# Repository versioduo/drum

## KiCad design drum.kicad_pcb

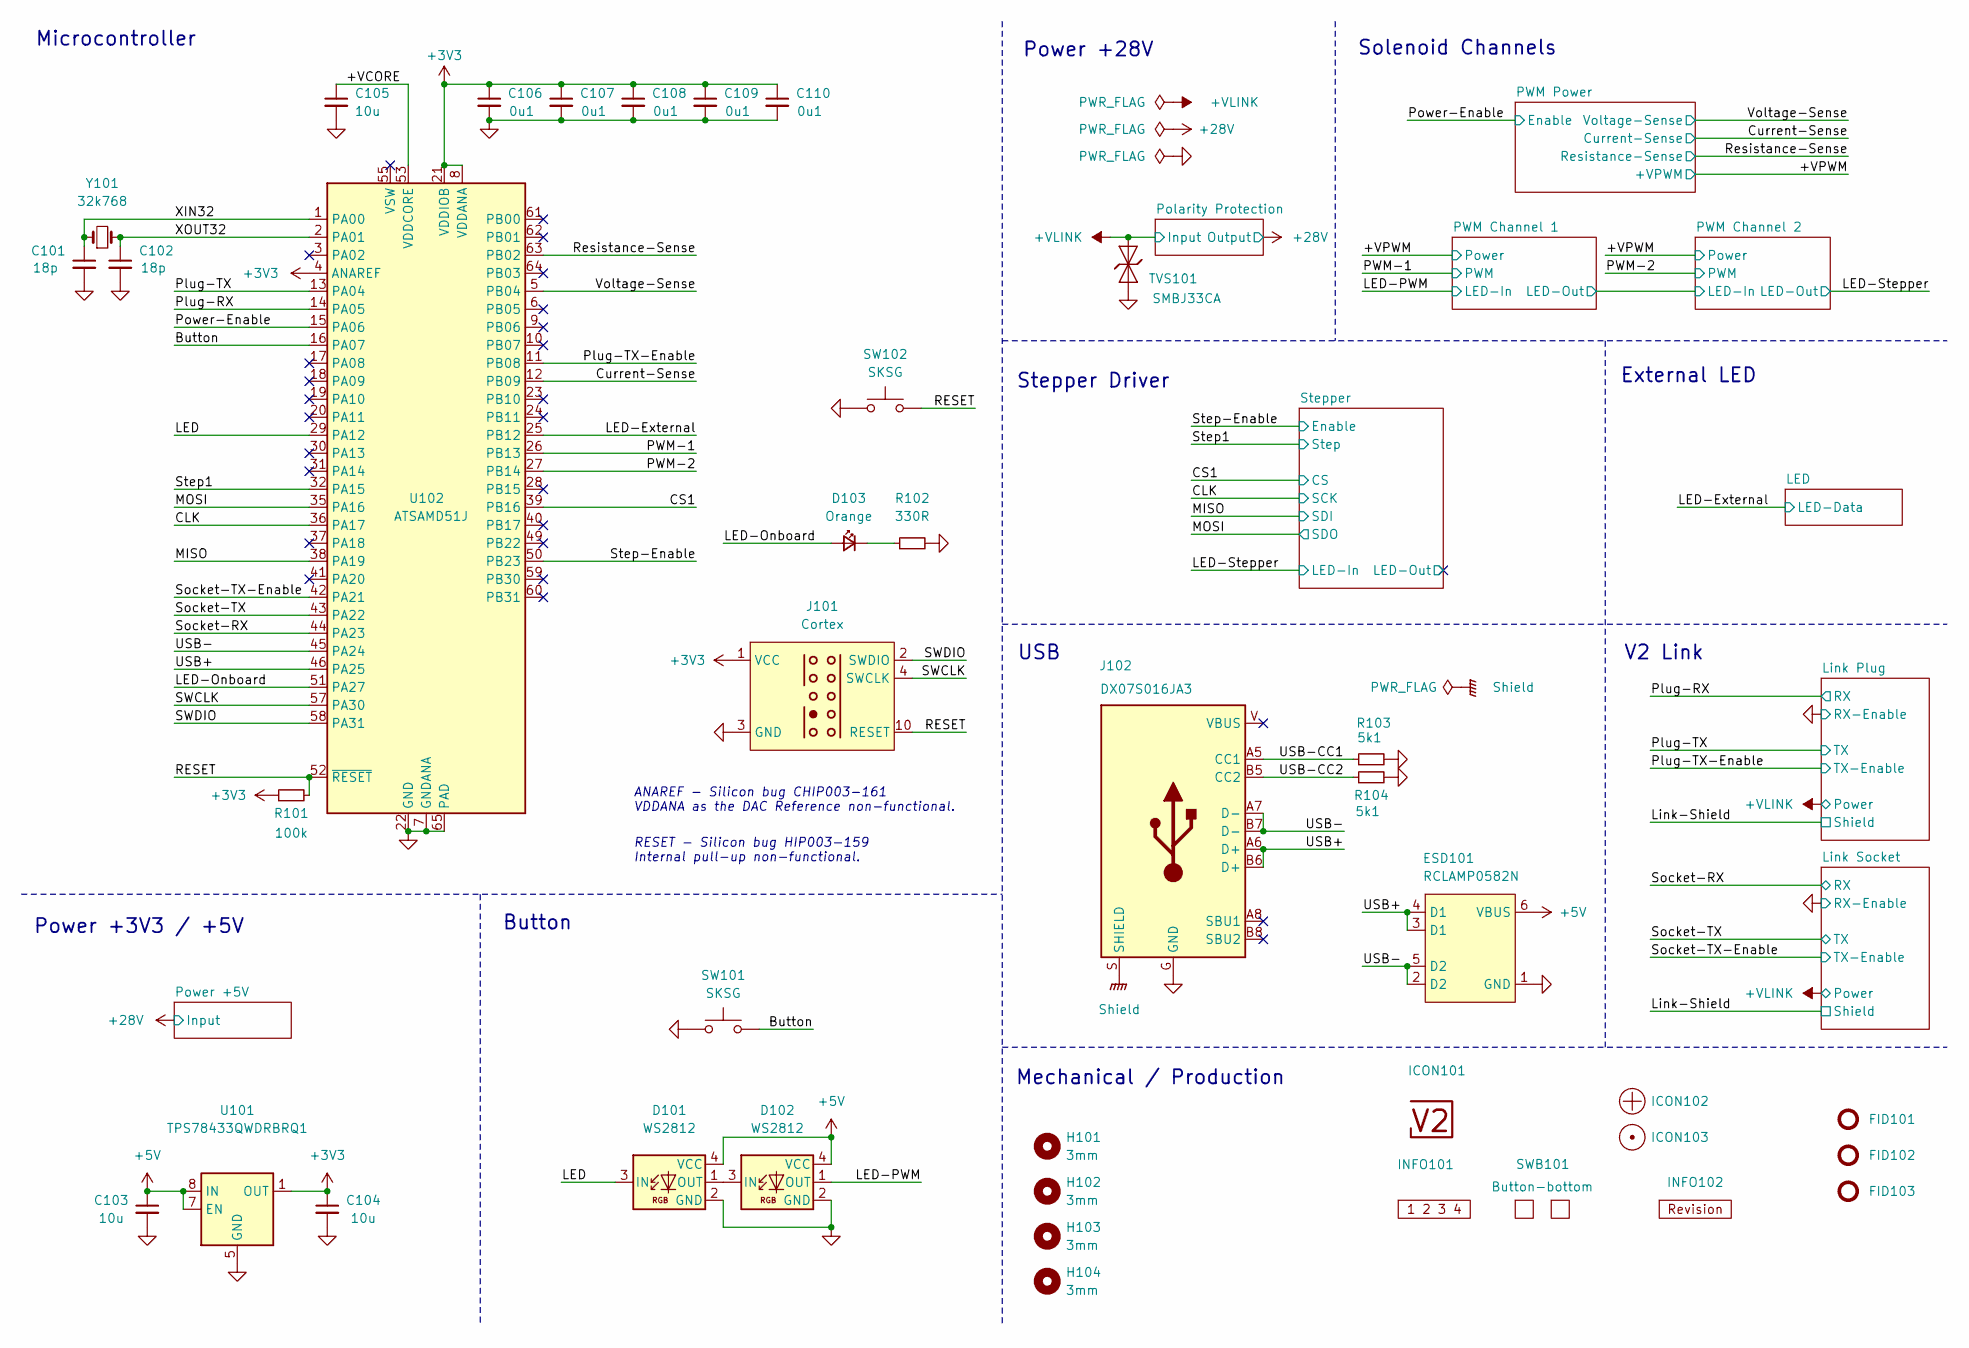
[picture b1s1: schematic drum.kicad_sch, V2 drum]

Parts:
C101, C102: 18p; C_1608; Rating 50V; Mouser 810-CGA3E2C0G1H180J
C103, C104: 10u; C_2012; Rating 25V; Mouser 810-C2012X5R1E106K
C105: 10u; C_1608; Rating 10V; Mouser 810-C1608X6S1A106M
C106, C107, C108, C109, C110: 0u1; C_1608; Rating 50V; Mouser 810-CGA3E2X7R1H104MA
D101, D102: WS2812; WS2812-2020; Rating 15mA; LCSC C965555
D103: Orange; LED_1608; Rating 605nm; Mouser 755-SML-D12D1WT86
ESD101: RCLAMP0582N; SLP1210N6; Rating 20kV; Mouser 947-RCLAMP0582N.TCT
FID101, FID102, FID103: Fiducial_Paste; Fiducial_0.5mm_Mask1mm_Paste
H101, H102, H103, H104: 3mm; MountingHole_3mm
ICON101: V2-logo; Logo_Small
ICON102: Plus; Plus_Small
ICON103: Dot; Dot_Small
INFO101: Layer_Numbers-6
INFO102: Revision
J101: Cortex
J102: DX07S016JA3; JAE_DX07S016JA3; Rating USB2.0; Mouser 656-DX07S016JA3R1500
R101: 100k; R_1608; Rating 100mW; Mouser 71-CRCW0603100KFKEAC
R102: 330R; R_1608; Rating 100mW; Mouser 71-CRCW0603330RFKEAC
R103, R104: 5k1; R_1608; Rating 100mW; Mouser 71-CRCW06035K10FKEAC
SW101, SW102: SKSG; Rating 1.6N; Mouser 688-SKSGACE010
SWB101: Button-bottom; PCB_Button-bottom
TVS101: SMBJ33CA; D_SMB; Rating 33V; Mouser 652-SMBJ33CA-Q
U101: TPS78433QWDRBRQ1; VSON-8-1_3x3mm_P0.65_EP1.65x2.4mm; Rating 300mA; Mouser 595-TPS78433QWDRBRQ1
U102: ATSAMD51J; QFN-64-1EP_9x9mm_P0.5mm_EP4.8x4.8mm_ThermalVias; Rating Cortex-M4F; Mouser 556-ATSAMD51J19AMU
Y101: 32k768; Crystal_SMD_3215-2Pin_3.2x1.5mm; Rating 10ppm; Mouser 815-ABS0716632.768KT

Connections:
+3V3: C104.1, C106.1, C107.1, C108.1, C109.1, C110.1, J101.1 (VCC), R101.1, U101.1 (OUT), U102.4 (ANAREF), U102.8 (VDDANA), U102.21 (VDDIOB), U102.34 (VDDIO), U102.48 (VDDIO), U102.56 (VDDIO); also elsewhere on the board
+5V: C103.1, D101.4 (VCC), D102.4 (VCC), ESD101.6 (VBUS), U101.6 (EN), U101.7 (EN), U101.8 (IN); also elsewhere on the board
/+VCORE: C105.1, U102.53 (VDDCORE)
/+VLINK: TVS101.2 (A); also elsewhere on the board
/Button: SW101.2, U102.16 (PA07)
/CLK: U102.36 (PA17); also elsewhere on the board
/CS1: U102.39 (PB16); also elsewhere on the board
/Current-Sense: U102.12 (PB09); also elsewhere on the board
/LED: D101.3 (IN), U102.29 (PA12)
/LED-External: U102.25 (PB12); also elsewhere on the board
/LED-Onboard: D103.2 (A), U102.51 (PA27)
/LED-PWM: D102.1 (OUT); also elsewhere on the board
/MISO: U102.38 (PA19); also elsewhere on the board
/MOSI: U102.35 (PA16); also elsewhere on the board
/PWM-1: U102.26 (PB13); also elsewhere on the board
/PWM-2: U102.27 (PB14); also elsewhere on the board
/Plug-RX: U102.14 (PA05); also elsewhere on the board
/Plug-TX: U102.13 (PA04); also elsewhere on the board
/Plug-TX-Enable: U102.11 (PB08); also elsewhere on the board
/Power-Enable: U102.15 (PA06); also elsewhere on the board
/RESET: J101.10 (RESET), R101.2, SW102.2, U102.52 (~RESET)
/Resistance-Sense: U102.63 (PB02); also elsewhere on the board
/SWCLK: J101.4 (SWCLK), U102.57 (PA30)
/SWDIO: J101.2 (SWDIO), U102.58 (PA31)
/Shield: J102.S (SHIELD)
/Socket-RX: U102.44 (PA23); also elsewhere on the board
/Socket-TX: U102.43 (PA22); also elsewhere on the board
/Socket-TX-Enable: U102.42 (PA21); also elsewhere on the board
/Step1: U102.32 (PA15); also elsewhere on the board
/Step-Enable: U102.50 (PB23); also elsewhere on the board
/USB+: ESD101.3 (D1), ESD101.4 (D1), J102.A6 (D+), J102.B6 (D+), U102.46 (PA25)
/USB-: ESD101.2 (D2), ESD101.5 (D2), J102.A7 (D-), J102.B7 (D-), U102.45 (PA24)
/USB-CC1: J102.A5 (CC1), R103.1
/USB-CC2: J102.B5 (CC2), R104.1
/Voltage-Sense: U102.5 (PB04); also elsewhere on the board
/XIN32: C101.1, U102.1 (PA00), Y101.1
/XOUT32: C102.1, U102.2 (PA01), Y101.2
GND: C101.2, C102.2, C103.2, C104.2, C105.2, C106.2, C107.2, C108.2, C109.2, C110.2, D101.2 (GND), D102.2 (GND), ESD101.1 (GND), J101.3 (GND), J101.5 (GND), J102.G (GND), R102.2, R103.2, R104.2, SW101.1, SW102.1, TVS101.1 (K), U101.5 (GND), U101.9 (GND), U102.7 (GNDANA), U102.22 (GND), U102.33 (GND), U102.47 (GND), U102.54 (GND), U102.65 (PAD); also elsewhere on the board
unnamed: D101.1 (OUT), D102.3 (IN)
unnamed: D103.1 (K), R102.1

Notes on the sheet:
﻿ANAREF - Silicon bug CHIP003-161 VDDANA as the DAC Reference non-functional.
Solenoid Channels
RESET - ﻿Silicon bug HIP003-159 Internal pull-up non-functional.
Button
USB
Mechanical / Production
External LED
Power +3V3 / +5V
Stepper Driver
V2 Link
Microcontroller
Power +28V

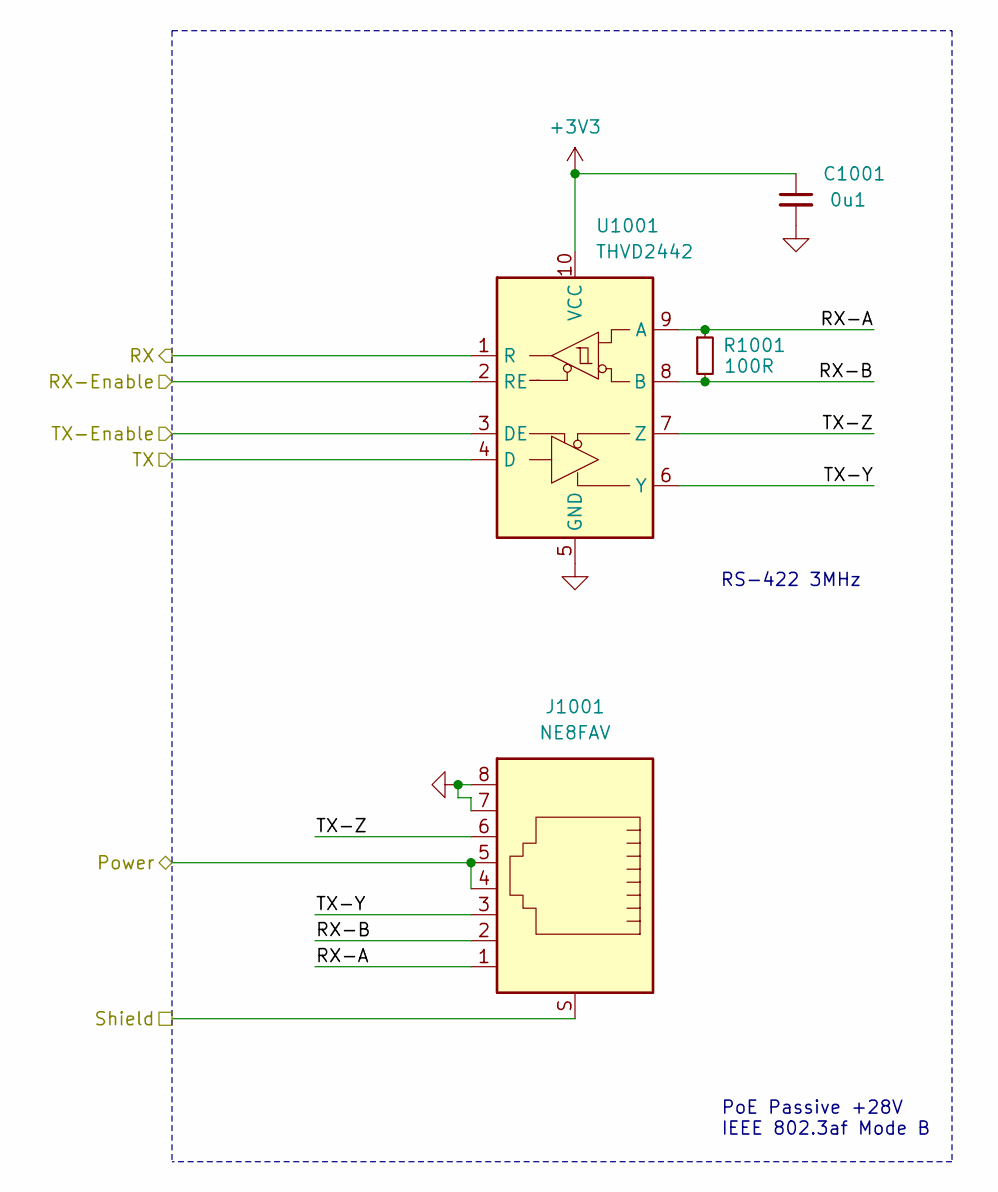
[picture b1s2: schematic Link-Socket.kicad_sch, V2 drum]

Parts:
C1001: 0u1; C_1608; Rating 50V; Mouser 810-CGA3E2X7R1H104MA
J1001: NE8FAV; Rating CAT5e; Mouser 568-NE8FAV-SD
R1001: 100R; R_1608; Rating 330mW; Mouser 71-CRCW0603100RFKEAH
U1001: THVD2442; VSON-10-4-1EP_3x3mm_P0.5mm_EP1.65x2.4mm_ThermalVias; Rating 20Mbps; Mouser 595-THVD2442DRCR

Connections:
+3V3: C1001.1, U1001.10 (VCC); also elsewhere on the board
/+VLINK: J1001.4, J1001.5; also elsewhere on the board
/Link Socket/RX-A: J1001.1, R1001.1, U1001.9 (A)
/Link Socket/RX-B: J1001.2, R1001.2, U1001.8 (B)
/Link Socket/TX-Y: J1001.3, U1001.6 (Y)
/Link Socket/TX-Z: J1001.6, U1001.7 (Z)
/Link-Shield: J1001.S; also elsewhere on the board
/Socket-RX: U1001.1 (R); also elsewhere on the board
/Socket-TX: U1001.4 (D); also elsewhere on the board
/Socket-TX-Enable: U1001.3 (DE); also elsewhere on the board
GND: C1001.2, J1001.7, J1001.8, U1001.2 (RE), U1001.5 (GND), U1001.11 (GND); also elsewhere on the board

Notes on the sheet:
PoE Passive +28V IEEE 802.3af Mode B
RS-422 3MHz

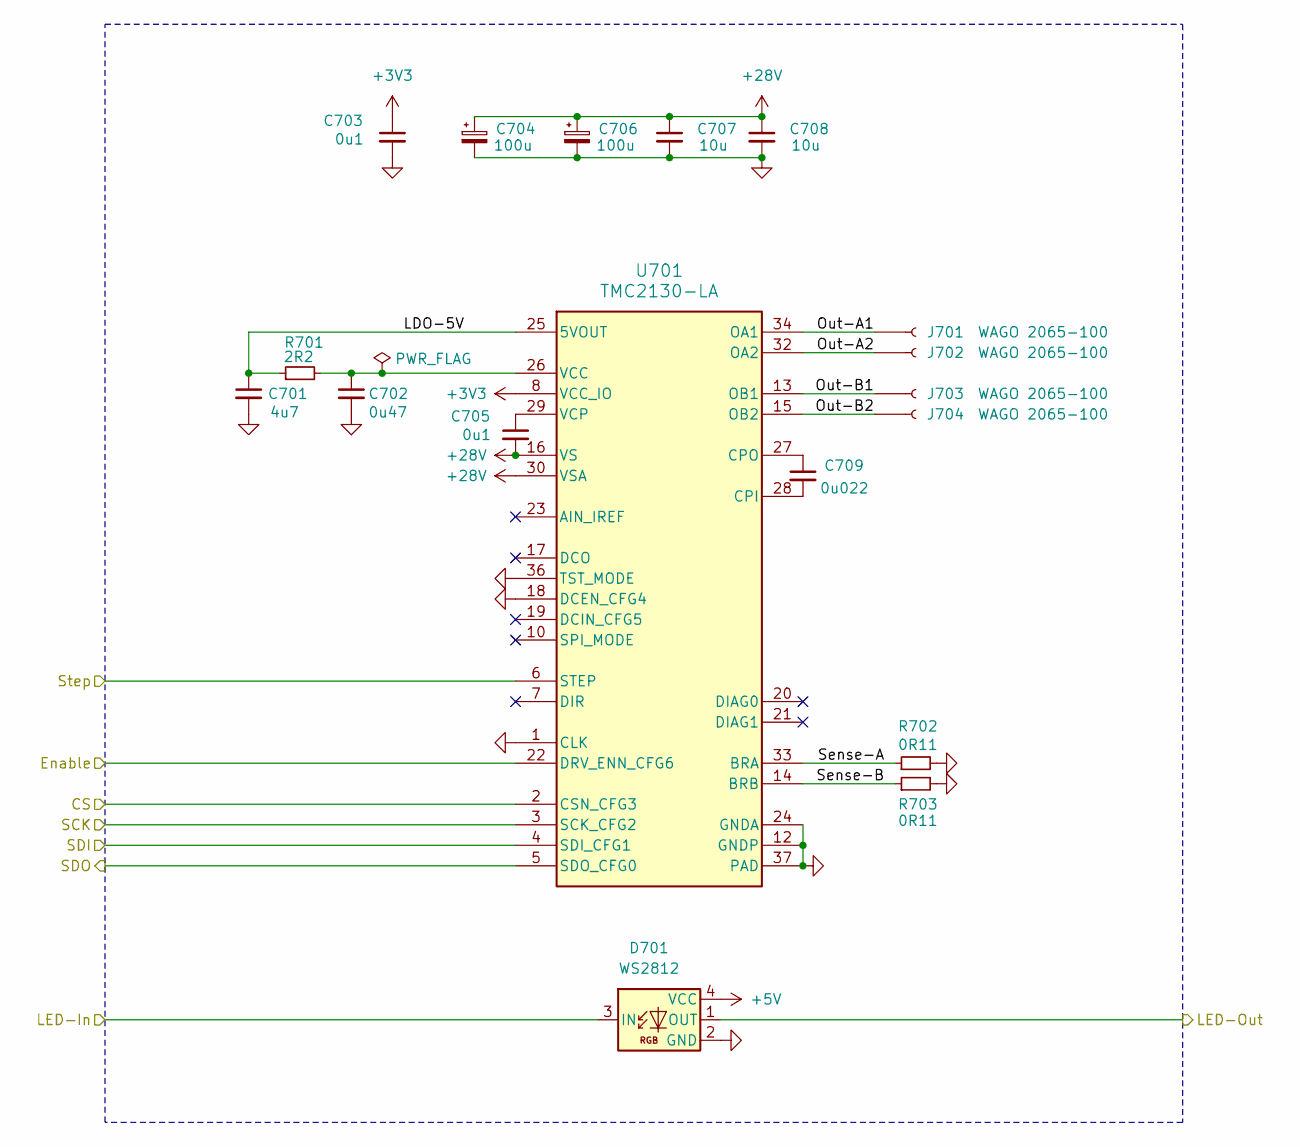
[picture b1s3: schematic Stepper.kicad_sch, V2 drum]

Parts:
C701: 4u7; C_1608; Rating 10V; Mouser 603-CC603KRX5R6BB475
C702: 0u47; C_1608; Rating 50V; Mouser 810-CGA3E3X7R1H474KB
C703, C705: 0u1; C_1608; Rating 50V; Mouser 810-CGA3E2X7R1H104MA
C704, C706: 100u; CP_Elec_6.3x7.7; Rating 35V; Mouser 667-EEE-FKV101XAL
C707, C708: 10u; C_3225; Rating 50V; Mouser 810-CNC6P1X7R1H106K2
C709: 0u022; C_1608; Rating 50V; Mouser 603-CC603KPX7R9BB223
D701: WS2812; WS2812-2020; Rating 15mA; LCSC C965555
J701, J702, J703, J704: WAGO 2065-100; 2065-100; Rating 9A
R701: 2R2; R_1608; Rating 500mW; Mouser 71-RCS06032R20JNEA
R702, R703: 0R11; R_2012; Rating 500mW; Mouser 667-ERJ-6DSFR11V
U701: TMC2130-LA; QFN-36-5X6; Rating 2A; LCSC C915795

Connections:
+3V3: C703.1, U701.8 (VCC_IO); also elsewhere on the board
+5V: D701.4 (VCC); also elsewhere on the board
+28V: C704.1, C705.2, C706.1, C707.1, C708.1, U701.16 (VS), U701.30 (VSA), U701.31 (VS); also elsewhere on the board
/CLK: U701.3 (SCK_CFG2); also elsewhere on the board
/CS1: U701.2 (CSN_CFG3); also elsewhere on the board
/LED-Stepper: D701.3 (IN); also elsewhere on the board
/MISO: U701.4 (SDI_CFG1); also elsewhere on the board
/MOSI: U701.5 (SDO_CFG0); also elsewhere on the board
/Step1: U701.6 (STEP); also elsewhere on the board
/Step-Enable: U701.22 (DRV_ENN_CFG6); also elsewhere on the board
/Stepper/LDO-5V: C701.1, R701.1, U701.25 (5VOUT)
/Stepper/LED-Out: D701.1 (OUT)
/Stepper/Out-A1: J701.1, U701.34 (OA1)
/Stepper/Out-A2: J702.1, U701.32 (OA2)
/Stepper/Out-B1: J703.1, U701.13 (OB1)
/Stepper/Out-B2: J704.1, U701.15 (OB2)
/Stepper/Sense-A: R702.1, U701.33 (BRA)
/Stepper/Sense-B: R703.1, U701.14 (BRB)
GND: C701.2, C702.2, C703.2, C704.2, C706.2, C707.2, C708.2, D701.2 (GND), R702.2, R703.2, U701.1 (CLK), U701.12 (GNDP), U701.18 (DCEN_CFG4), U701.24 (GNDA), U701.35 (GNDP), U701.36 (TST_MODE), U701.37 (PAD); also elsewhere on the board
unnamed: C709.2, U701.28 (CPI)
unnamed: C709.1, U701.27 (CPO)
unnamed: C702.1, R701.2, U701.26 (VCC)
unnamed: C705.1, U701.29 (VCP)

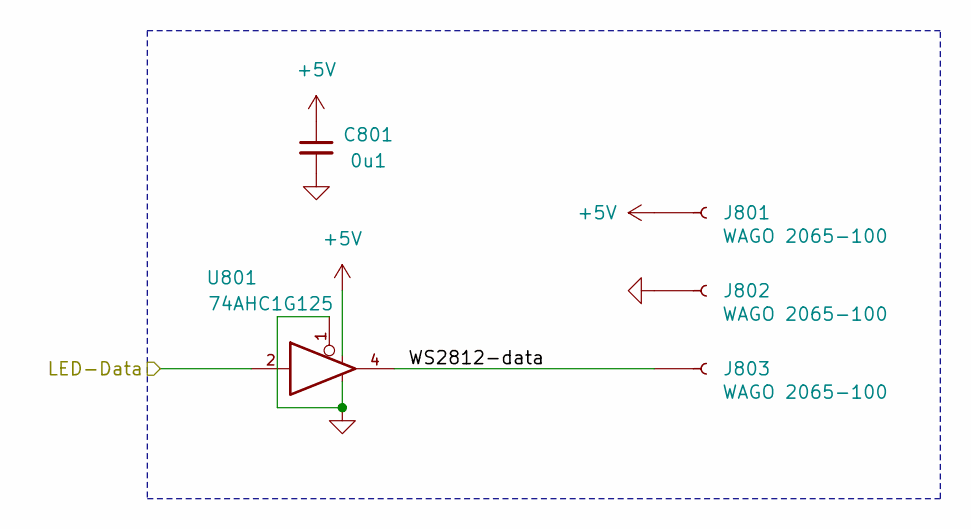
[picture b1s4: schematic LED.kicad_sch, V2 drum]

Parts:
C801: 0u1; C_1608; Rating 50V; Mouser 810-CGA3E2X7R1H104MA
J801, J802, J803: WAGO 2065-100; 2065-100; Rating 9A
U801: 74AHC1G125; SOT-23-5; Rating 8mA; Mouser 595-SN74AHC1G125DBVR

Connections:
+5V: C801.1, J801.1, U801.5; also elsewhere on the board
/LED-External: U801.2; also elsewhere on the board
/LED/WS2812-data: J803.1, U801.4
GND: C801.2, J802.1, U801.1, U801.3; also elsewhere on the board

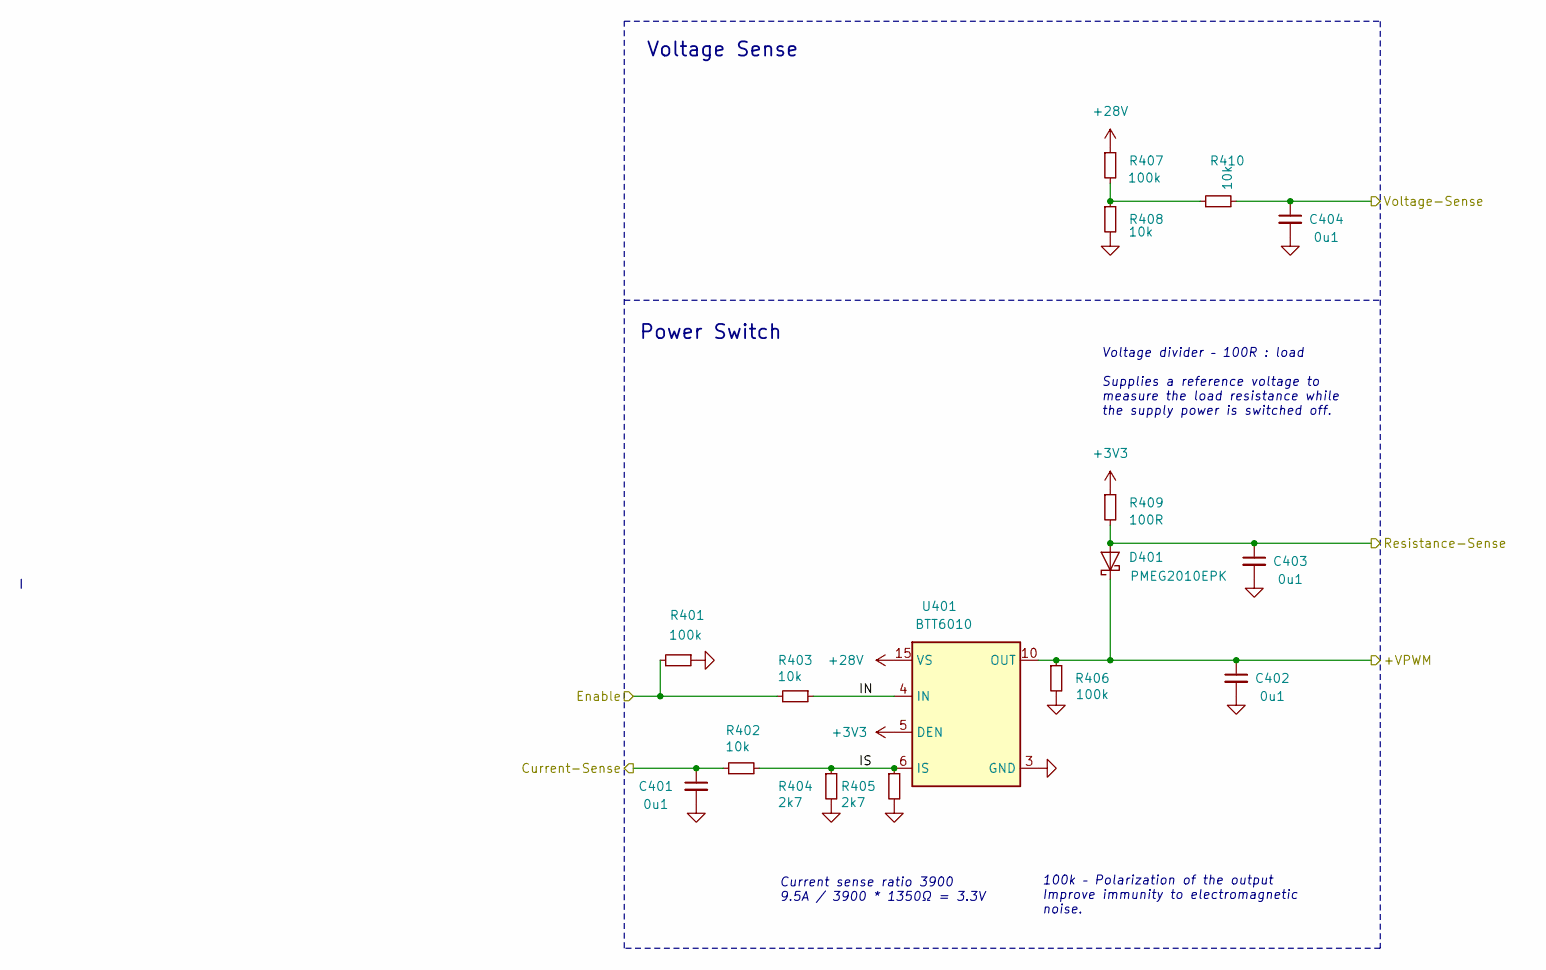
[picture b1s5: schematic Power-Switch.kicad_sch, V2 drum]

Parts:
C401, C402, C403, C404: 0u1; C_1608; Rating 50V; Mouser 810-CGA3E2X7R1H104MA
D401: PMEG2010EPK; D_SOD-1608; Rating 20V; Mouser 771-PMEG2010EPK
R401, R406, R407: 100k; R_1608; Rating 100mW; Mouser 71-CRCW0603100KFKEAC
R402, R403, R408, R410: 10k; R_1608; Rating 100mW; Mouser 71-CRCW060310K0FKEAC
R404, R405: 2k7; R_1608; Rating 100mW; Mouser 71-CRCW06032K70FKEAC
R409: 100R; R_1608; Rating 330mW; Mouser 71-CRCW0603100RFKEAH
U401: BTT6010; PG-TDS0-14; Rating 36V; Mouser 726-BTT60101ERBXUMA1

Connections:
+3V3: R409.1, U401.5 (DEN); also elsewhere on the board
+28V: R407.1, U401.15 (VS); also elsewhere on the board
/+VPWM: C402.1, D401.1 (K), R406.1, U401.10 (OUT), U401.11 (OUT), U401.12 (OUT); also elsewhere on the board
/Current-Sense: C401.1, R402.1; also elsewhere on the board
/PWM Power/IN: R403.1, U401.4 (IN)
/PWM Power/IS: R402.2, R404.1, R405.1, U401.6 (IS)
/Power-Enable: R401.2, R403.2; also elsewhere on the board
/Resistance-Sense: C403.1, D401.2 (A), R409.2; also elsewhere on the board
/Voltage-Sense: C404.1, R410.2; also elsewhere on the board
GND: C401.2, C402.2, C403.2, C404.2, R401.1, R404.2, R405.2, R406.2, R408.2, U401.3 (GND); also elsewhere on the board
unnamed: R407.2, R408.1, R410.1

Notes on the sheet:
100k – Polarization of the output Improve immunity to electromagnetic noise.
Current sense ratio 3900 9.5A / 3900 * 1350Ω = 3.3V
Voltage Sense
Power Switch
Voltage divider – 100R : load Supplies a reference voltage to measure the load resistance while the supply power is switched off.

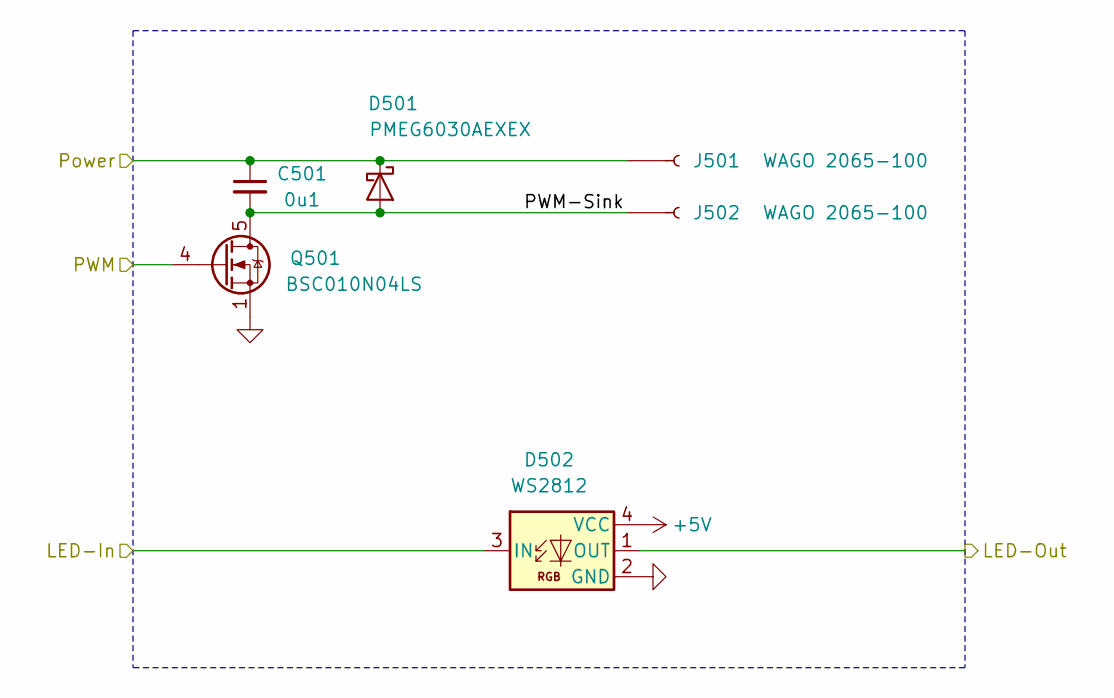
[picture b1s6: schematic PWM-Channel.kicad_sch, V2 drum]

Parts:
C501: 0u1; C_1608; Rating 50V; Mouser 810-CGA3E2X7R1H104MA
D501: PMEG6030AEXEX; D_SOD-123HP; Rating 60V; Mouser 771-PMEG6030AEXEX
D502: WS2812; WS2812-2020; Rating 15mA; LCSC C965555
J501, J502: WAGO 2065-100; 2065-100; Rating 9A
Q501: BSC010N04LS; TDSON-8-FL; Rating 40V; Mouser 726-BSC010N04LS

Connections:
+5V: D502.4 (VCC); also elsewhere on the board
/+VPWM: C501.1, D501.1 (K), J501.1; also elsewhere on the board
/LED-PWM: D502.3 (IN); also elsewhere on the board
/PWM Channel 1/LED-Out: D502.1 (OUT); also elsewhere on the board
/PWM Channel 1/PWM-Sink: C501.2, D501.2 (A), J502.1, Q501.5 (D)
/PWM-1: Q501.4 (G); also elsewhere on the board
GND: D502.2 (GND), Q501.1 (S); also elsewhere on the board

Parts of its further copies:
C601: 0u1; C_1608; Rating 50V; Mouser 810-CGA3E2X7R1H104MA
D601: PMEG6030AEXEX; D_SOD-123HP; Rating 60V; Mouser 771-PMEG6030AEXEX
D602: WS2812; WS2812-2020; Rating 15mA; LCSC C965555
J601, J602: WAGO 2065-100; 2065-100; Rating 9A
Q601: BSC010N04LS; TDSON-8-FL; Rating 40V; Mouser 726-BSC010N04LS

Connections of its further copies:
+5V: D602.4 (VCC); also elsewhere on the board
/+VPWM: C601.1, D601.1 (K), J601.1; also elsewhere on the board
/LED-Stepper: D602.1 (OUT); also elsewhere on the board
/PWM Channel 1/LED-Out: D602.3 (IN); also elsewhere on the board
/PWM Channel 2/PWM-Sink: C601.2, D601.2 (A), J602.1, Q601.5 (D)
/PWM-2: Q601.4 (G); also elsewhere on the board
GND: D602.2 (GND), Q601.1 (S); also elsewhere on the board

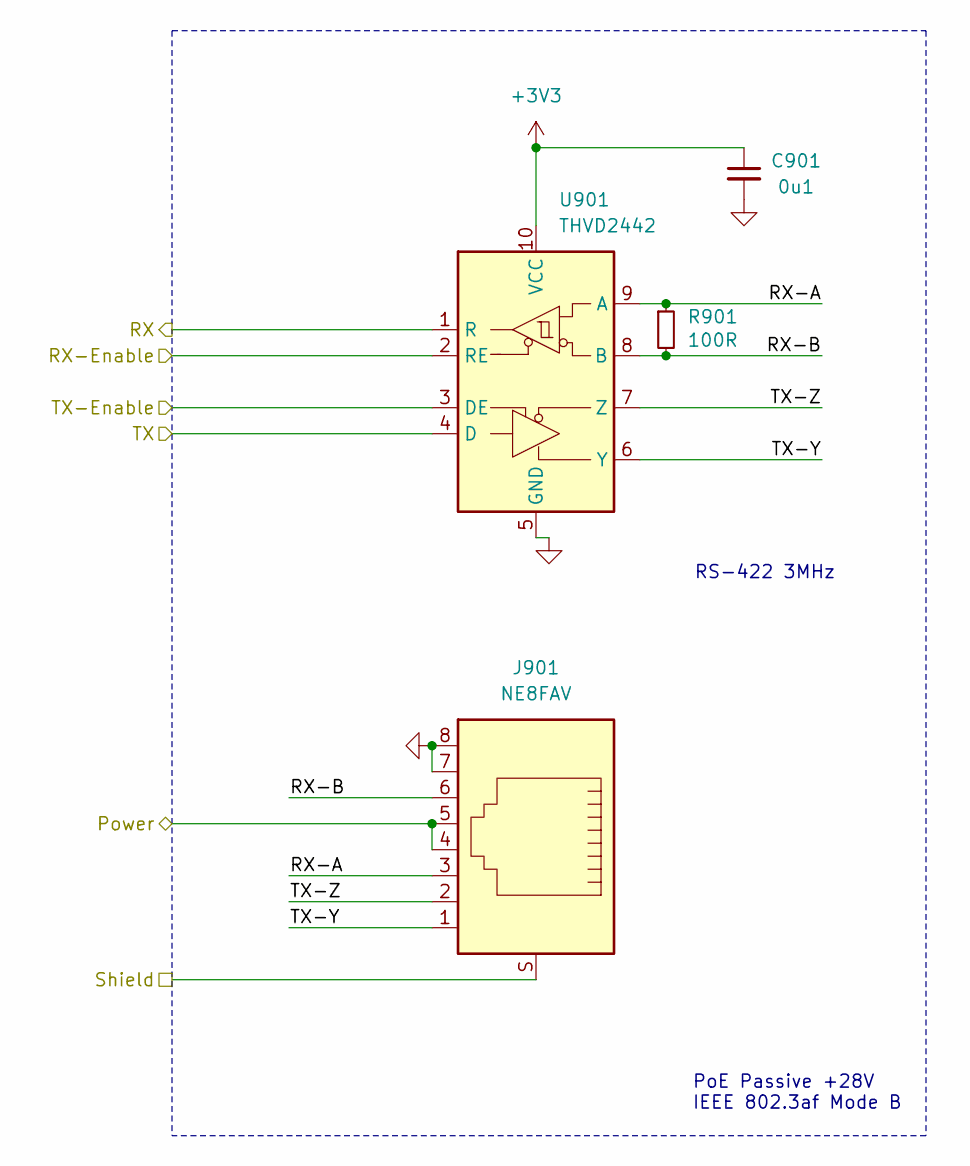
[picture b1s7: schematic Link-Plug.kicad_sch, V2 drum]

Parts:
C901: 0u1; C_1608; Rating 50V; Mouser 810-CGA3E2X7R1H104MA
J901: NE8FAV; Rating CAT5e; Mouser 568-NE8FAV-SD
R901: 100R; R_1608; Rating 330mW; Mouser 71-CRCW0603100RFKEAH
U901: THVD2442; VSON-10-4-1EP_3x3mm_P0.5mm_EP1.65x2.4mm_ThermalVias; Rating 20Mbps; Mouser 595-THVD2442DRCR

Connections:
+3V3: C901.1, U901.10 (VCC); also elsewhere on the board
/+VLINK: J901.4, J901.5; also elsewhere on the board
/Link Plug/RX-A: J901.3, R901.1, U901.9 (A)
/Link Plug/RX-B: J901.6, R901.2, U901.8 (B)
/Link Plug/TX-Y: J901.1, U901.6 (Y)
/Link Plug/TX-Z: J901.2, U901.7 (Z)
/Link-Shield: J901.S; also elsewhere on the board
/Plug-RX: U901.1 (R); also elsewhere on the board
/Plug-TX: U901.4 (D); also elsewhere on the board
/Plug-TX-Enable: U901.3 (DE); also elsewhere on the board
GND: C901.2, J901.7, J901.8, U901.2 (RE), U901.5 (GND), U901.11 (GND); also elsewhere on the board

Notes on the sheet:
RS-422 3MHz
PoE Passive +28V IEEE 802.3af Mode B

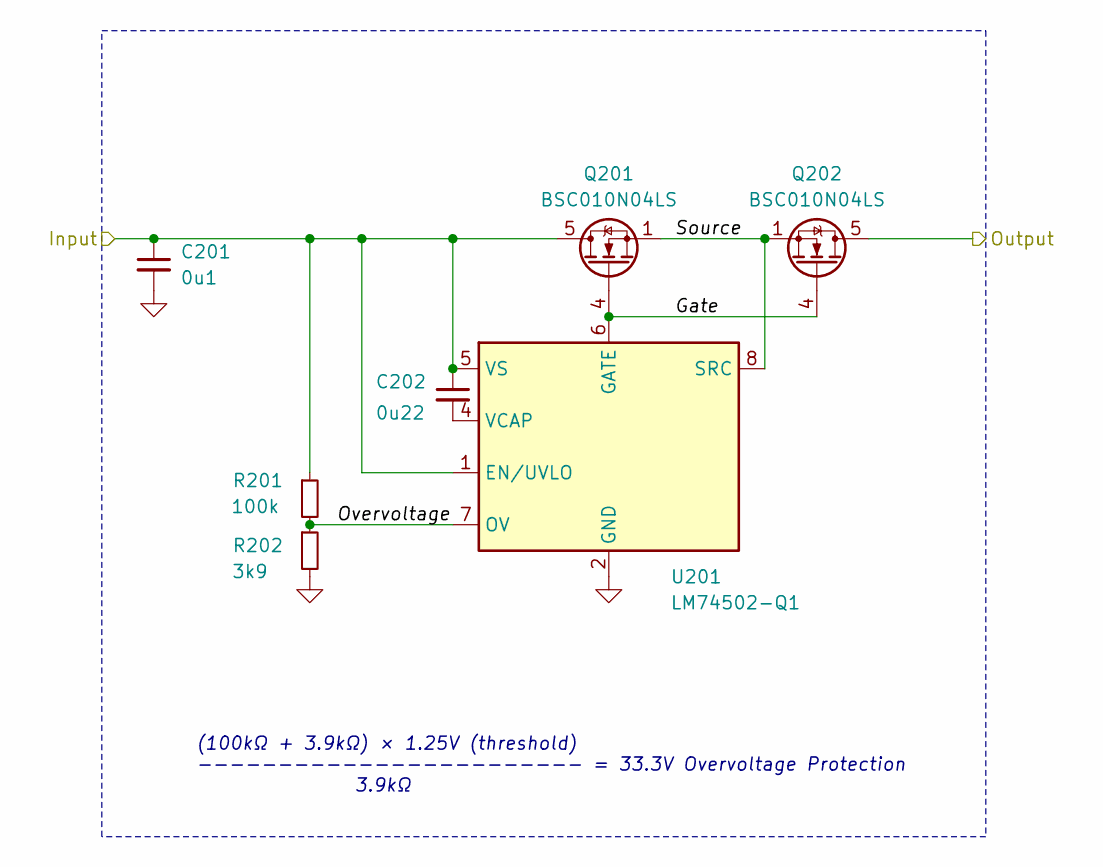
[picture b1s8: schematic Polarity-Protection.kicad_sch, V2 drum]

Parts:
C201: 0u1; C_1608; Rating 50V; Mouser 810-CGA3E2X7R1H104MA
C202: 0u22; C_1608; Rating 50V; Mouser 603-CC0603JRX79BB224
Q201, Q202: BSC010N04LS; TDSON-8-FL; Rating 40V; Mouser 726-BSC010N04LS
R201: 100k; R_1608; Rating 100mW; Mouser 71-CRCW0603100KFKEAC
R202: 3k9; R_1608; Rating 100mW; Mouser 71-CRCW06033K90FKEAC
U201: LM74502-Q1; SOT-23-8; Rating 60uA; Mouser 595-LM74502QDDFRQ1

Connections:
+28V: Q202.5 (D); also elsewhere on the board
/+VLINK: C201.1, C202.1, Q201.5 (D), R201.1, U201.1 (EN/UVLO), U201.5 (VS); also elsewhere on the board
/Polarity Protection/Gate: Q201.4 (G), Q202.4 (G), U201.6 (GATE)
/Polarity Protection/Overvoltage: R201.2, R202.1, U201.7 (OV)
/Polarity Protection/Source: Q201.1 (S), Q202.1 (S), U201.8 (SRC)
GND: C201.2, R202.2, U201.2 (GND); also elsewhere on the board
unnamed: C202.2, U201.4 (VCAP)

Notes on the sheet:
(100kΩ + 3.9kΩ) × 1.25V (threshold) ------------------------ = 33.3V Overvoltage Protection 3.9kΩ

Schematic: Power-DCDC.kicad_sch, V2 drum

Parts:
C301: 10u; C_3225; Rating 50V; Mouser 810-CNC6P1X7R1H106K2
C302: 0u1; C_1608; Rating 50V; Mouser 810-CGA3E2X7R1H104MA
C303: 1u; C_1608; Rating 50V; Mouser 810-CGA3E3X7R1H105K0
C304, C305: 22u; C_3225; Rating 25V; Mouser 810-CGA6P3X7R1E226M5
U301: TPSM33620S5QRDNRQ1; QFN-11; Rating 2A; Mouser 595-SM33620S5QRDNRQ1

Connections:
+5V: C304.1, C305.1, U301.4 (VOUT), U301.9 (FB); also elsewhere on the board
+28V: C301.1, C302.1, U301.2 (EN), U301.3 (VIN); also elsewhere on the board
/Power +5V/Vcc: C303.1, U301.8 (VCC)
GND: C301.2, C302.2, C303.2, C304.2, C305.2, U301.10 (GND), U301.11 (MODE); also elsewhere on the board

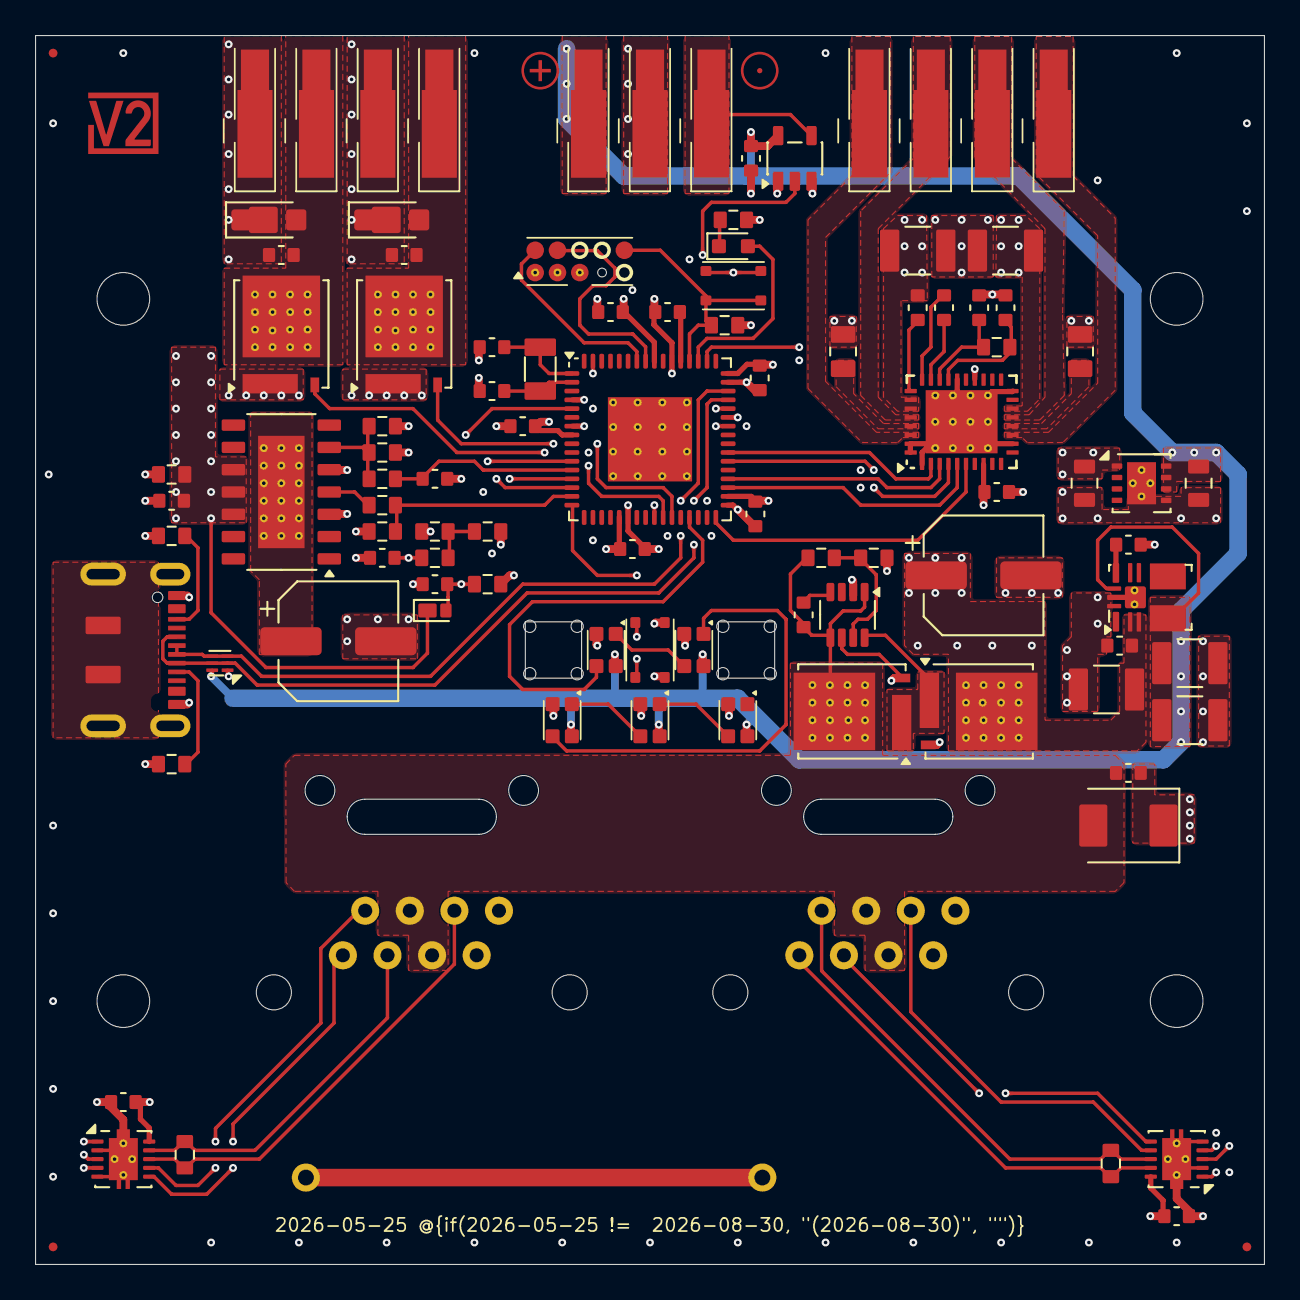
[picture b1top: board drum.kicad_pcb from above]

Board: 6 copper layers, 70.0 x 70.0 mm, 111 parts (0 on the bottom side), 74 nets.

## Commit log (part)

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2025-12-28 Import
2026-01-01 Refresh
2026-01-14 Update parts
2026-01-27 Update library
2026-02-10 Use date as revision
2026-02-13 Replace Order_Number
2026-03-11 Replace diode
2026-03-14 Update ESD suppressor
2026-03-31 Replace step-down
2026-05-11 Good Bye Imperial
2026-05-27 Switch to 6 layer
2026-06-08 Fix fiducial
